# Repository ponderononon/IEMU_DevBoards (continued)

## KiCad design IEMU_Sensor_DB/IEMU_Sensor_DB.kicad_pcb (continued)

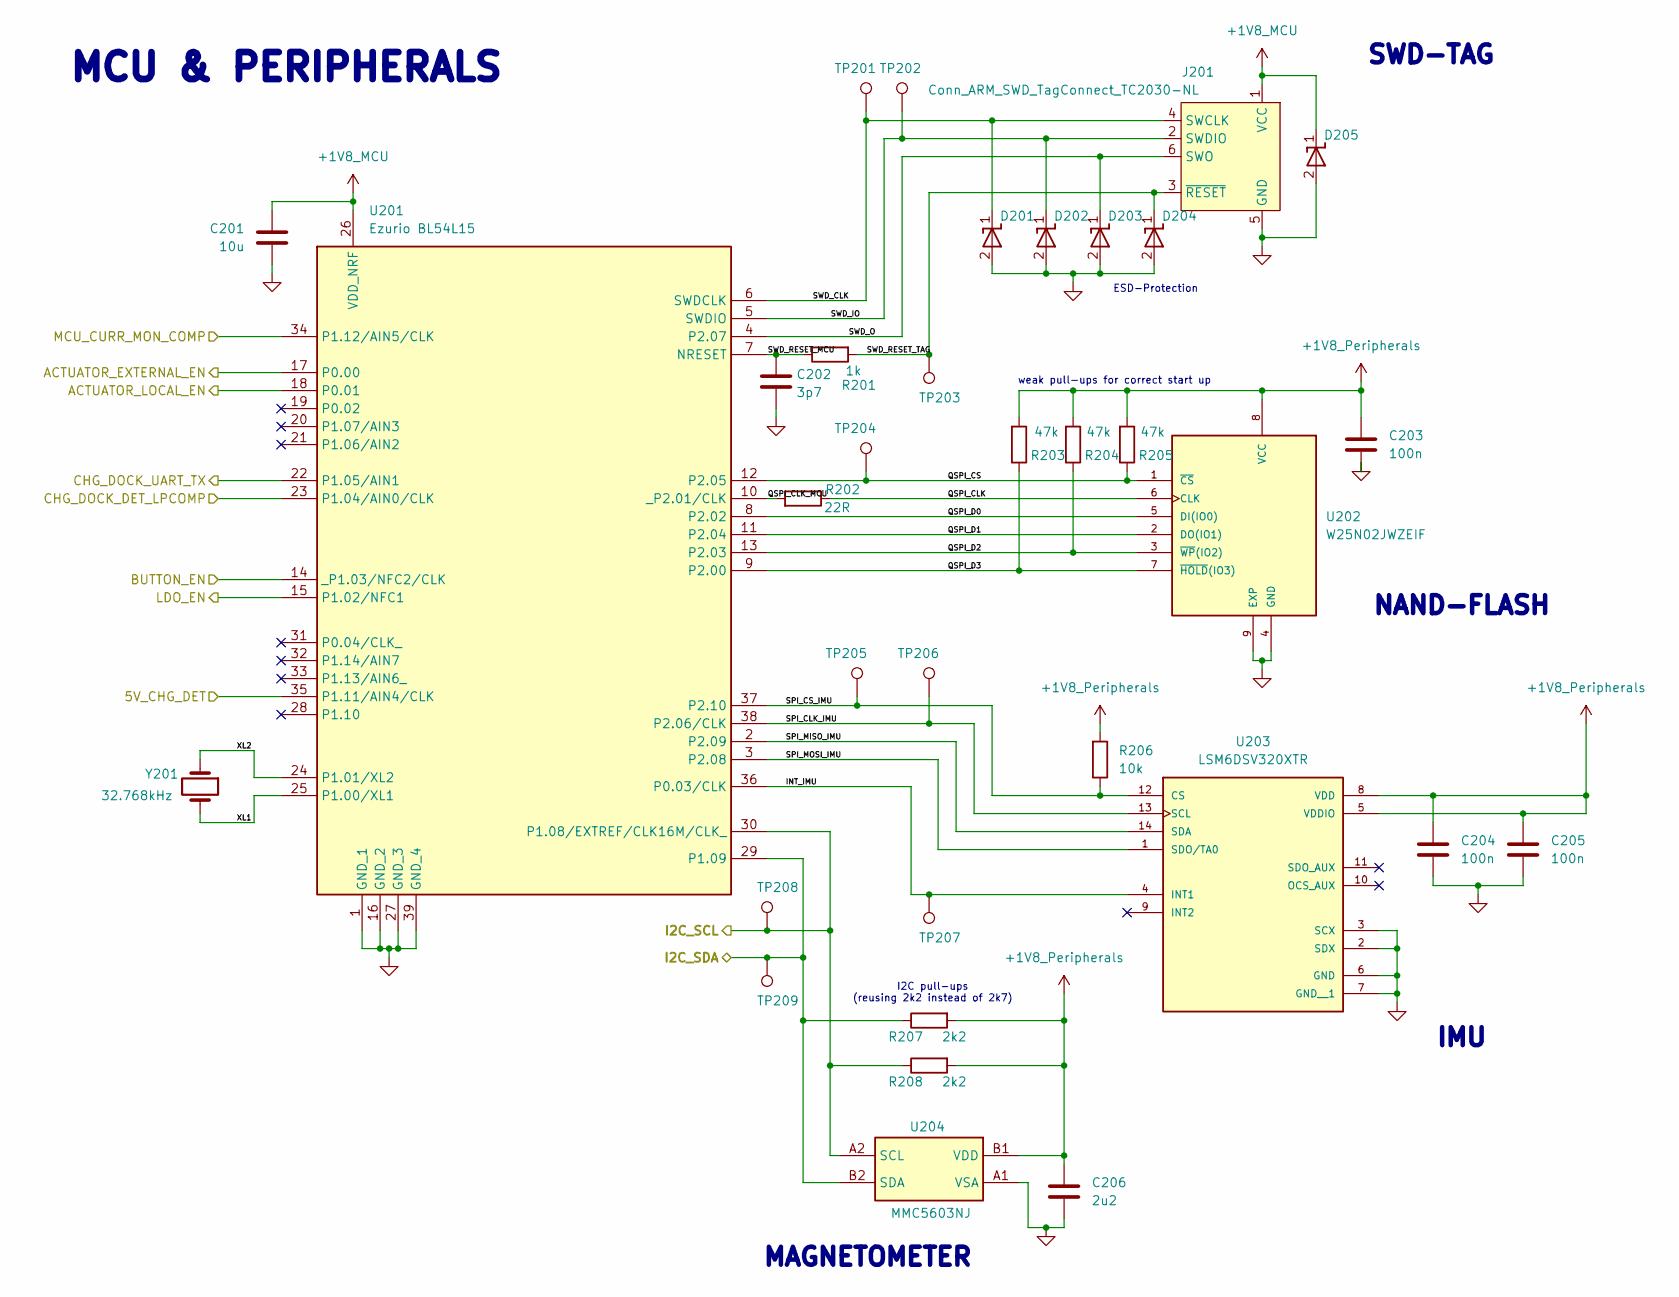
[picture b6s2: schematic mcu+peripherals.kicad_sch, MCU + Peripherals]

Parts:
C201: 10u; C_0603_1608Metric; Manufacturer_Part_Number CL10A106MA8NRNC; LCSC C96446
C202: 3p7; C_0402_1005Metric; Manufacturer_Part_Number GCM1555C1H3R7CA16D; LCSC C2189484
C203, C204, C205: 100n; C_0402_1005Metric; Manufacturer_Part_Number CL05B104KO5NNNC; LCSC C1525
C206: 2u2; C_0402_1005Metric; Manufacturer_Part_Number CL05A225MQ5NSNC; LCSC C12530
D201, D202, D203, D204, D205: RCLAMP01811PW.C; DIODFN100X60X55-2N; Manufacturer_Part_Number RCLAMP01811PW.C
J201: Conn_ARM_SWD_TagConnect_TC2030-NL; Tag-Connect_TC2030-IDC-NL_2x03_P1.27mm_Vertical
R201: 1k; R_0402_1005Metric; Manufacturer_Part_Number 0402WGF1001TCE; LCSC C11702
R202: 22R; R_0603_1608Metric; Manufacturer_Part_Number 0603WAF220JT5E; LCSC C23345
R203, R204, R205: 47k; R_0402_1005Metric; Manufacturer_Part_Number 0402WGF4702TCE; LCSC C25792
R206: 10k; R_0402_1005Metric; Manufacturer_Part_Number 0402WGF1002TCE; LCSC C25744
R207, R208: 2k2; R_0402_1005Metric; Manufacturer_Part_Number 0402WGF2201TCE; LCSC C25879
TP201, TP202, TP203, TP204, TP205, TP206, TP207, TP208, TP209: TestPoint_Pad_D1.0mm
U201: Ezurio BL54L15; BL54L15; Manufacturer_Part_Number 453-00001C
U202: W25N02JWZEIF; IC_W25N04KVZEIR; Manufacturer_Part_Number W25N02JWZEIF; LCSC C2962014
U203: LSM6DSV320XTR; LGA-14_3x2.5mm_P0.5mm_LayoutBorder3x4y; Manufacturer_Part_Number LSM6DSV320XTR; LCSC C26633007
U204: MMC5603NJ; Manufacturer_Part_Number MMC5603NJ; LCSC C404328
Y201: 32.768kHz; Crystal_SMD_3215-2Pin_3.2x1.5mm; Manufacturer_Part_Number SC-32S32.768kHz20PPM9pF; LCSC C97605

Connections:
+1V8_MCU: C201.1, D205.1 (I/O), J201.1 (VCC), U201.26 (VDD_NRF); also elsewhere on the board
+1V8_Peripherals: C203.1, C204.1, C205.1, C206.1, R203.1, R204.1, R205.1, R206.1, R207.1, R208.1, U202.8 (VCC), U203.5 (VDDIO), U203.8 (VDD), U204.B1 (VDD); also elsewhere on the board
/1_Power/5V_CHG_DET: U201.35 (P1.11/AIN4/CLK); also elsewhere on the board
/1_Power/CHG_DOCK_DET_LPCOMP: U201.23 (P1.04/AIN0/CLK); also elsewhere on the board
/1_Power/CHG_DOCK_UART_TX: U201.22 (P1.05/AIN1); also elsewhere on the board
/1_Power/LDO_EN: U201.15 (P1.02/NFC1); also elsewhere on the board
/1_Power/MCU_CURR_MON_COMP: U201.34 (P1.12/AIN5/CLK); also elsewhere on the board
/1_Power/NPM_SCL: R208.2, TP208.1, U201.30 (P1.08/EXTREF/CLK16M/CLK_), U204.A2 (SCL); also elsewhere on the board
/1_Power/NPM_SDA: R207.2, TP209.1, U201.29 (P1.09), U204.B2 (SDA); also elsewhere on the board
/2_nRF Module & NAND Flash + IMU + Magnetometer/ACTUATOR_EXTERNAL_EN: U201.17 (P0.00); also elsewhere on the board
/2_nRF Module & NAND Flash + IMU + Magnetometer/ACTUATOR_LOCAL_EN: U201.18 (P0.01); also elsewhere on the board
/2_nRF Module & NAND Flash + IMU + Magnetometer/BUTTON_EN: U201.14 (_P1.03/NFC2/CLK); also elsewhere on the board
/2_nRF Module & NAND Flash + IMU + Magnetometer/INT_IMU: TP207.1, U201.36 (P0.03/CLK), U203.4 (INT1)
/2_nRF Module & NAND Flash + IMU + Magnetometer/QSPI_CLK: R202.2, U202.6 (CLK)
/2_nRF Module & NAND Flash + IMU + Magnetometer/QSPI_CLK_MCU: R202.1, U201.10 (_P2.01/CLK)
/2_nRF Module & NAND Flash + IMU + Magnetometer/QSPI_CS: R205.2, TP204.1, U201.12 (P2.05), U202.1 (~CS)
/2_nRF Module & NAND Flash + IMU + Magnetometer/QSPI_D0: U201.8 (P2.02), U202.5 (DI(IO0))
/2_nRF Module & NAND Flash + IMU + Magnetometer/QSPI_D1: U201.11 (P2.04), U202.2 (DO(IO1))
/2_nRF Module & NAND Flash + IMU + Magnetometer/QSPI_D2: R204.2, U201.13 (P2.03), U202.3 (~WP(IO2))
/2_nRF Module & NAND Flash + IMU + Magnetometer/QSPI_D3: R203.2, U201.9 (P2.00), U202.7 (~HOLD(IO3))
/2_nRF Module & NAND Flash + IMU + Magnetometer/SPI_CLK_IMU: TP206.1, U201.38 (P2.06/CLK), U203.13 (SCL)
/2_nRF Module & NAND Flash + IMU + Magnetometer/SPI_CS_IMU: R206.2, TP205.1, U201.37 (P2.10), U203.12 (CS)
/2_nRF Module & NAND Flash + IMU + Magnetometer/SPI_MISO_IMU: U201.2 (P2.09), U203.14 (SDA)
/2_nRF Module & NAND Flash + IMU + Magnetometer/SPI_MOSI_IMU: U201.3 (P2.08), U203.1 (SDO/TA0)
/2_nRF Module & NAND Flash + IMU + Magnetometer/SWD_CLK: D201.1 (I/O), J201.4 (SWCLK), TP201.1, U201.6 (SWDCLK)
/2_nRF Module & NAND Flash + IMU + Magnetometer/SWD_IO: D202.1 (I/O), J201.2 (SWDIO), TP202.1, U201.5 (SWDIO)
/2_nRF Module & NAND Flash + IMU + Magnetometer/SWD_O: D203.1 (I/O), J201.6 (SWO), U201.4 (P2.07)
/2_nRF Module & NAND Flash + IMU + Magnetometer/SWD_RESET_MCU: C202.1, R201.2, U201.7 (NRESET)
/2_nRF Module & NAND Flash + IMU + Magnetometer/SWD_RESET_TAG: D204.1 (I/O), J201.3 (~RESET), R201.1, TP203.1
/2_nRF Module & NAND Flash + IMU + Magnetometer/XL1: U201.25 (P1.00/XL1), Y201.2
/2_nRF Module & NAND Flash + IMU + Magnetometer/XL2: U201.24 (P1.01/XL2), Y201.1
GND: C201.2, C202.2, C203.2, C204.2, C205.2, C206.2, D201.2 (GND), D202.2 (GND), D203.2 (GND), D204.2 (GND), D205.2 (GND), J201.5 (GND), U201.1 (GND_1), U201.16 (GND_2), U201.27 (GND_3), U201.39 (GND_4), U202.4 (GND), U202.9 (EXP), U203.2 (SDX), U203.3 (SCX), U203.6 (GND), U203.7 (GND__1), U204.A1 (VSA); also elsewhere on the board

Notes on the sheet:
I2C pull-ups (reusing 2k2 instead of 2k7)
MAGNETOMETER
IMU
SWD-TAG
MCU & PERIPHERALS
NAND-FLASH
weak pull-ups for correct start up
ESD-Protection

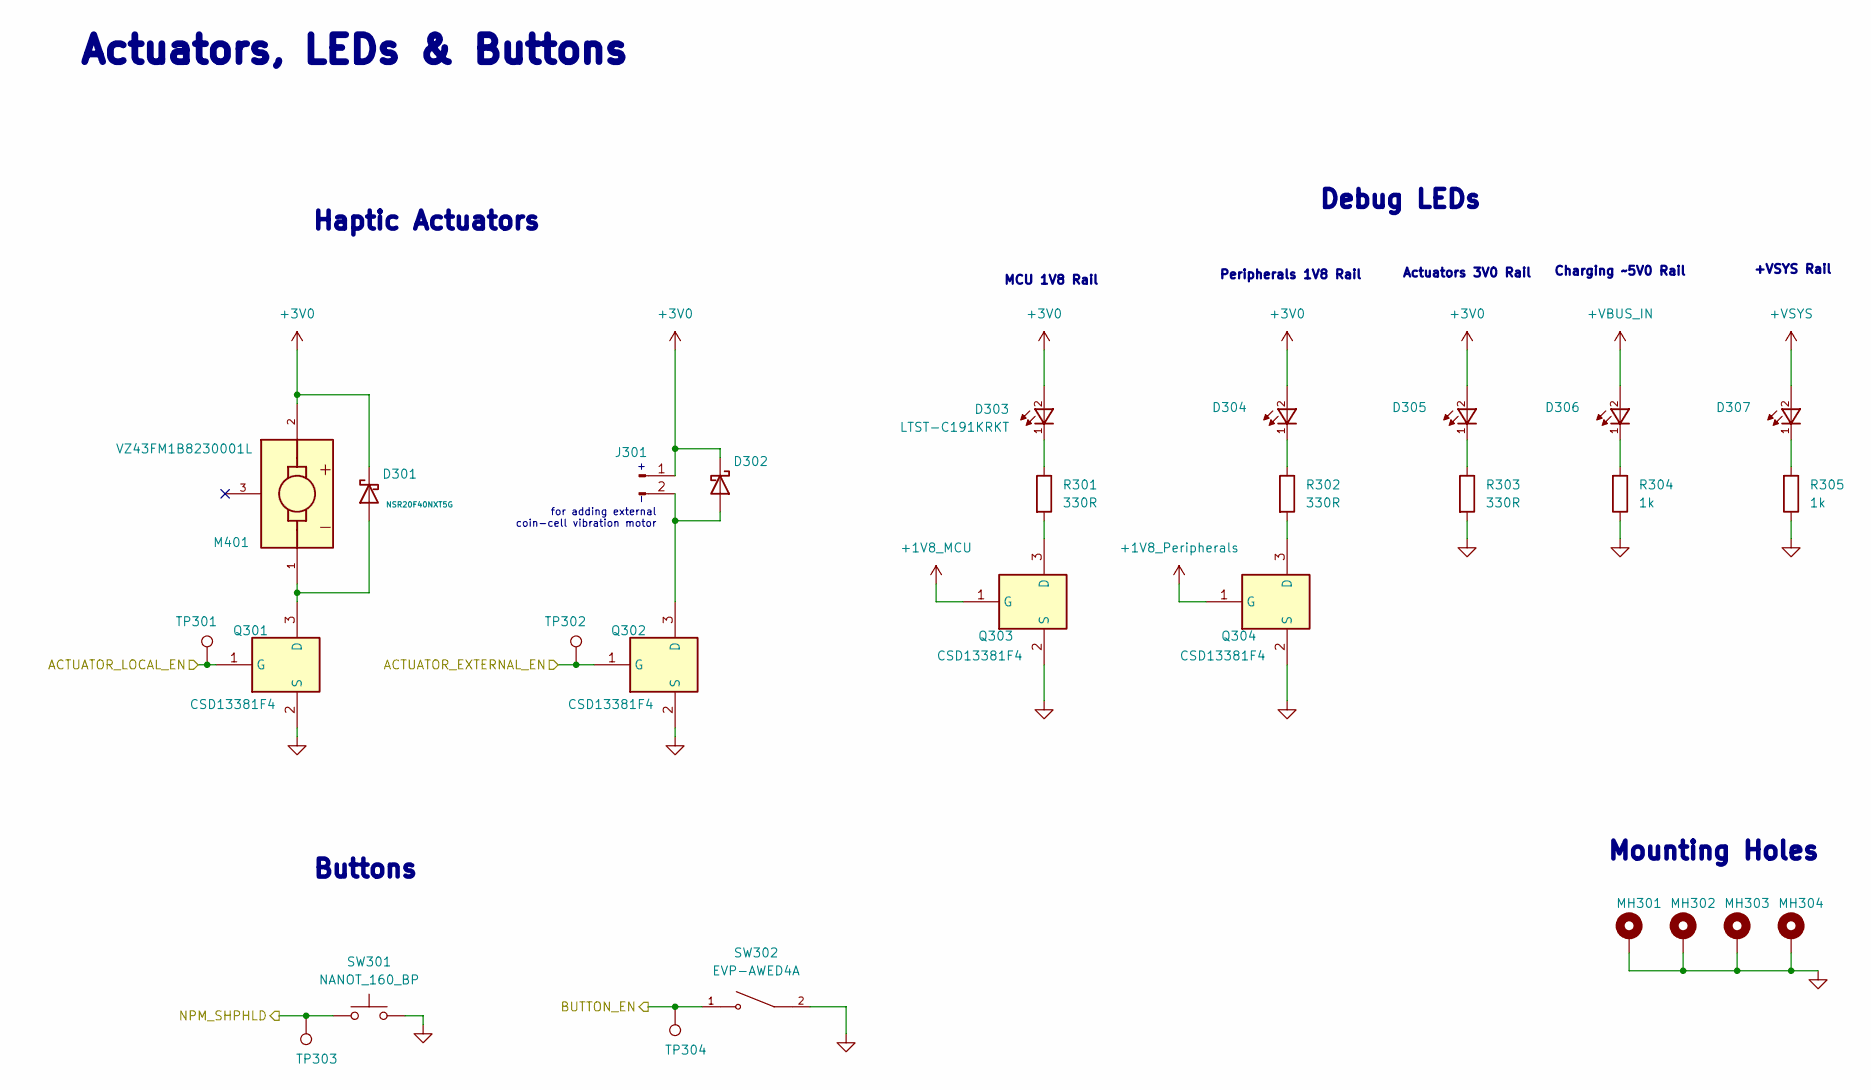
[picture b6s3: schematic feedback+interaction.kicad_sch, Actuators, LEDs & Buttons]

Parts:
D301, D302: D_Schottky_2A_40V_0603; 0603_DSN; Manufacturer_Part_Number NSR20F40NXT5G; LCSC C153761
D303, D304, D305, D306, D307: LTST-C191KRKT; Manufacturer_Part_Number LTST-C191KRKT; LCSC C125099
J301: Conn_01x02_Pin; SolderWire-0.5sqmm_1x02_P4.6mm_D0.9mm_OD2.1mm
M401: VZ43FM1B8230001L; XDCR_VZ43FM1B8230001L; Manufacturer_Part_Number VZ43FM1B8230001L; LCSC C7467059
MH301, MH302, MH303, MH304: MountingHole_Pad; MountingHole_2.2mm_M2_Pad_Via
Q301, Q302, Q303, Q304: CSD13381F4; DFN100X60X35-3N; Manufacturer_Part_Number CSD13381F4; LCSC C179868
R301, R302, R303: 330R; R_0402_1005Metric; Manufacturer_Part_Number 0402WGF3300TCE; LCSC C25104
R304, R305: 1k; R_0402_1005Metric; Manufacturer_Part_Number 0402WGF1001TCE; LCSC C11702
SW301: NANOT_160_BP; NANOT160BP; Manufacturer_Part_Number NANOT160BP; LCSC C2760983
SW302: EVP-AWED4A; SW_EVP-AWED4A; Manufacturer_Part_Number EVP-AWBD2A
TP301, TP302, TP303, TP304: TestPoint_Pad_D1.0mm

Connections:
+1V8_MCU: Q303.1 (G); also elsewhere on the board
+1V8_Peripherals: Q304.1 (G); also elsewhere on the board
+3V0: D301.1 (K), D302.1 (K), D303.2, D304.2, D305.2, J301.1, M401.2; also elsewhere on the board
+VBUS_IN: D306.2; also elsewhere on the board
+VSYS: D307.2; also elsewhere on the board
/1_Power/NPM_SHPHLD: SW301.1, TP303.1; also elsewhere on the board
/2_nRF Module & NAND Flash + IMU + Magnetometer/ACTUATOR_EXTERNAL_EN: Q302.1 (G), TP302.1; also elsewhere on the board
/2_nRF Module & NAND Flash + IMU + Magnetometer/ACTUATOR_LOCAL_EN: Q301.1 (G), TP301.1; also elsewhere on the board
/2_nRF Module & NAND Flash + IMU + Magnetometer/BUTTON_EN: SW302.1, TP304.1; also elsewhere on the board
GND: MH301.1, MH302.1, MH303.1, MH304.1, Q301.2 (S), Q302.2 (S), Q303.2 (S), Q304.2 (S), R303.2, R304.2, R305.2, SW301.2, SW302.2; also elsewhere on the board
unnamed: D301.2 (A), M401.1, Q301.3 (D)
unnamed: D302.2 (A), J301.2, Q302.3 (D)
unnamed: D303.1, R301.1
unnamed: D304.1, R302.1
unnamed: D305.1, R303.1
unnamed: D306.1, R304.1
unnamed: D307.1, R305.1
unnamed: Q303.3 (D), R301.2
unnamed: Q304.3 (D), R302.2

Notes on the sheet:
Actuators 3V0 Rail
Mounting Holes
Buttons
Actuators, LEDs & Buttons
Peripherals 1V8 Rail
for adding external coin-cell vibration motor
+VSYS Rail
MCU 1V8 Rail
Haptic Actuators
Charging ~5V0 Rail
Debug LEDs

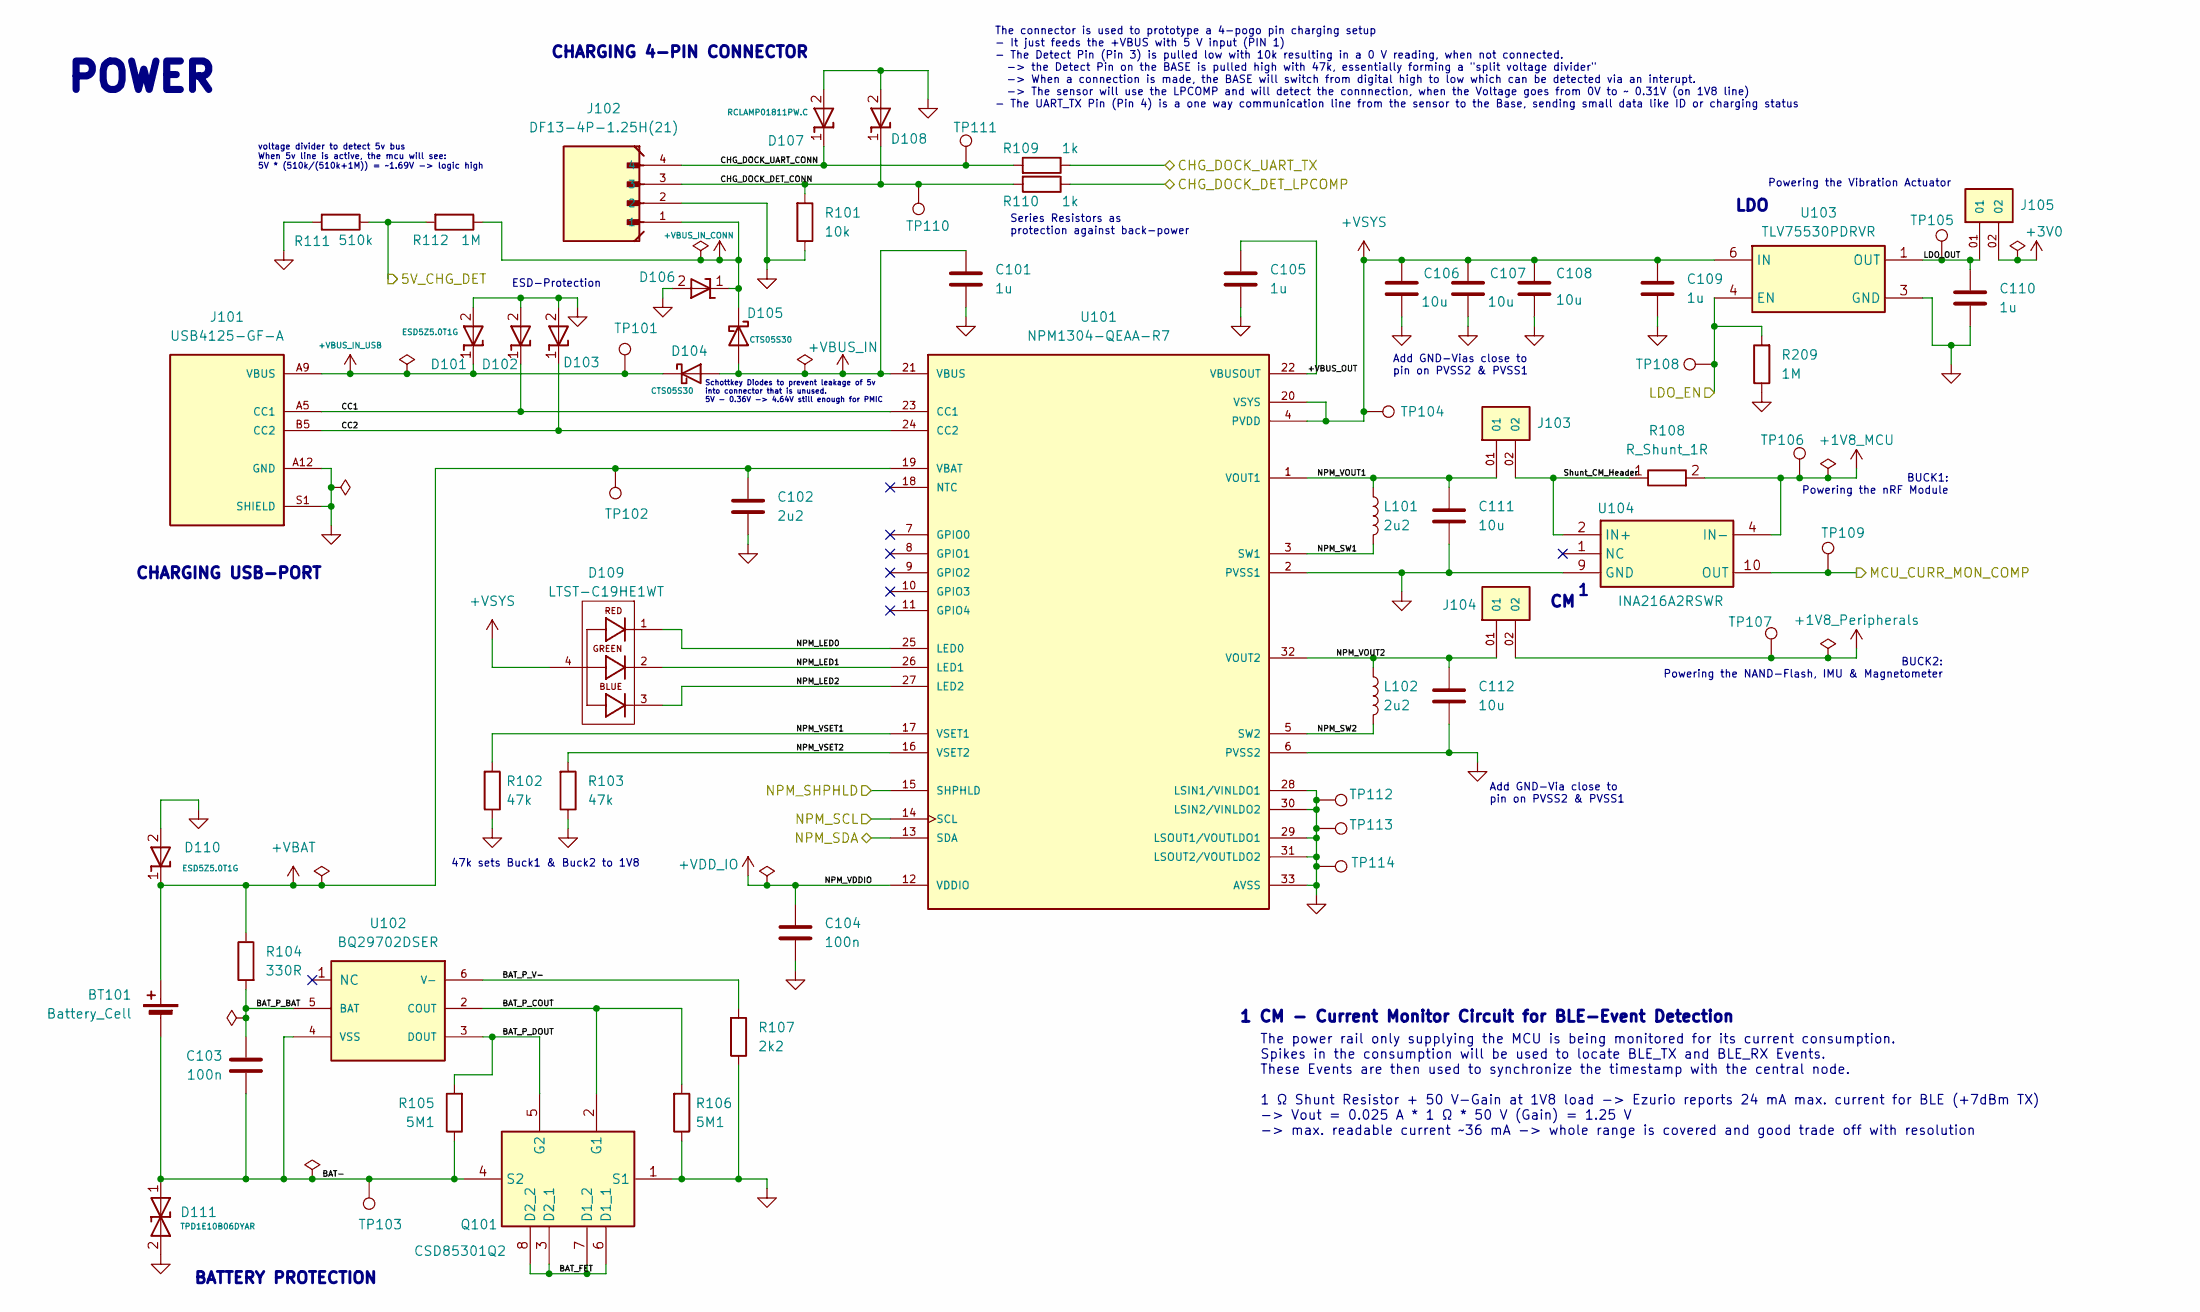
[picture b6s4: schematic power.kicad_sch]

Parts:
BT101: Battery_Cell; CoinCell_LIR1455_LBY2
C101, C105, C109, C110: 1u; C_0402_1005Metric; Manufacturer_Part_Number CL05A105KA5NQNC; LCSC C52923
C102: 2u2; C_0402_1005Metric; Manufacturer_Part_Number CL05A225MQ5NSNC; LCSC C12530
C103, C104: 100n; C_0402_1005Metric; Manufacturer_Part_Number CL05B104KO5NNNC; LCSC C1525
C106, C107, C108, C111, C112: 10u; C_0603_1608Metric; Manufacturer_Part_Number CL10A106MA8NRNC; LCSC C96446
D101, D102, D103, D106, D110: ESD5Z5.0T1G; D_SOD-523_1; Manufacturer_Part_Number ESD5Z5.0T1G; LCSC C82044
D104, D105: CTS05S30; D_SOD-882; Manufacturer_Part_Number CTS05S30
D107, D108: RCLAMP01811PW.C; DIODFN100X60X55-2N; Manufacturer_Part_Number RCLAMP01811PW.C
D109: LTST-C19HE1WT; LED_LTST-C19HE1WT; Manufacturer_Part_Number LTST-C19HE1WT; LCSC C458749
D111: TPD1E10B06DYAR; D_SOD-523; Manufacturer_Part_Number TPD1E10B06DYAR; LCSC C3712135
J101: USB4125-GF-A; GCT_USB4125-GF-A_REVA2; Manufacturer_Part_Number USB4125-GF-A; LCSC C3151650
J102: DF13-4P-1.25H(21); Manufacturer_Part_Number DF13-4P-1.25H(21); LCSC C597872
J103, J104, J105: SAMTEC_MTSW-101-X-X-D-X; Manufacturer_Part_Number MTSW-101-07-T-D-240
L101, L102: 2u2; L_0603_1608Metric; Manufacturer_Part_Number LSCNB1608HKT2R2MD; LCSC C6079477
Q101: CSD85301Q2; Manufacturer_Part_Number CSD85301Q2; LCSC C544396
R101: 10k; R_0402_1005Metric; Manufacturer_Part_Number 0402WGF1002TCE; LCSC C25744
R102, R103: 47k; R_0402_1005Metric; Manufacturer_Part_Number 0402WGF4702TCE; LCSC C25792
R104: 330R; R_0402_1005Metric; Manufacturer_Part_Number 0402WGF3300TCE; LCSC C25104
R105, R106: 5M1; R_0402_1005Metric; Manufacturer_Part_Number RC0402JR-075M1L; LCSC C137855
R107: 2k2; R_0402_1005Metric; Manufacturer_Part_Number 0402WGF2201TCE; LCSC C25879
R108: R_Shunt_1R; R_0402_1005Metric; Manufacturer_Part_Number RLP73K1E1R0FTDF; LCSC C2074826
R109, R110: 1k; R_0402_1005Metric; Manufacturer_Part_Number 0402WGF1001TCE; LCSC C11702
R111: 510k; R_0603_1608Metric; Manufacturer_Part_Number 0603WAF5103T5E; LCSC C23192
R112, R209: 1M; R_0402_1005Metric; Manufacturer_Part_Number 0402WGF1004TCE; LCSC C26083
TP101, TP102, TP103, TP104, TP105, TP106, TP107, TP108, TP109, TP110, TP111, TP112, TP113, TP114: TestPoint_Pad_D1.0mm
U101: NPM1304-QEAA-R7; QFN50P500X500X90-33N; Manufacturer_Part_Number NPM1304-QEAA-R7; LCSC C49448846
U102: BQ29702DSER; WSON-6_1.5x1.5mm_P0.5mm; Manufacturer_Part_Number BQ29702DSER; LCSC C2872632
U103: TLV75530PDRVR; WSON-6-1EP_2x2mm_P0.65mm_EP1x1.6mm_ThermalVias; Manufacturer_Part_Number TLV75530PDRVR; LCSC C2859948
U104: INA216A2RSWR; Texas_RSW0010A_UQFN-10_1.4x1.8mm_P0.4mm; Manufacturer_Part_Number INA216A2RSWR; LCSC C2653823

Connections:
+1V8_MCU: R108.2, TP106.1, U104.4 (IN-), U104.5 (IN-); also elsewhere on the board
+1V8_Peripherals: J104.02, TP107.1; also elsewhere on the board
+3V0: J105.02; also elsewhere on the board
+VBAT: BT101.1 (+), C102.1, D110.1 (I/O), R104.1, TP102.1, U101.19 (VBAT)
+VBUS_IN: C101.1, D104.2 (A), D105.2 (A), U101.21 (VBUS); also elsewhere on the board
+VBUS_IN_CONN: D105.1 (K), D106.1 (I/O), J102.1, R112.2
+VBUS_IN_USB: D101.1 (I/O), D104.1 (K), J101.A9 (VBUS), J101.B9 (VBUS), TP101.1
+VDD_IO: C104.1, U101.12 (VDDIO)
+VSYS: C106.1, C107.1, C108.1, C109.1, D109.4, TP104.1, U101.4 (PVDD), U101.20 (VSYS), U103.6 (IN); also elsewhere on the board
/1_Power/5V_CHG_DET: R111.2, R112.1; also elsewhere on the board
/1_Power/+VBUS_OUT: C105.1, U101.22 (VBUSOUT)
/1_Power/BAT-: BT101.2 (-), C103.2, D111.1 (I/O), Q101.4 (S2), R105.2, TP103.1, U102.4 (VSS)
/1_Power/BAT_FET: Q101.3 (D2_1), Q101.6 (D1_1), Q101.7 (D1_2), Q101.8 (D2_2)
/1_Power/BAT_P_BAT: C103.1, R104.2, U102.5 (BAT)
/1_Power/BAT_P_COUT: Q101.2 (G1), R106.1, U102.2 (COUT)
/1_Power/BAT_P_DOUT: Q101.5 (G2), R105.1, U102.3 (DOUT)
/1_Power/BAT_P_V-: R107.1, U102.6 (V-)
/1_Power/CC1: D102.1 (I/O), J101.A5 (CC1), U101.23 (CC1)
/1_Power/CC2: D103.1 (I/O), J101.B5 (CC2), U101.24 (CC2)
/1_Power/CHG_DOCK_DET_CONN: D108.1 (I/O), J102.3, R101.1, R110.1, TP110.1
/1_Power/CHG_DOCK_DET_LPCOMP: R110.2; also elsewhere on the board
/1_Power/CHG_DOCK_UART_CONN: D107.1 (I/O), J102.4, R109.1, TP111.1
/1_Power/CHG_DOCK_UART_TX: R109.2; also elsewhere on the board
/1_Power/LDO_EN: R209.1, TP108.1, U103.4 (EN); also elsewhere on the board
/1_Power/LDO_OUT: C110.1, J105.01, TP105.1, U103.1 (OUT)
/1_Power/MCU_CURR_MON_COMP: TP109.1, U104.10 (OUT); also elsewhere on the board
/1_Power/NPM_LED0: D109.1, U101.25 (LED0)
/1_Power/NPM_LED1: D109.2, U101.26 (LED1)
/1_Power/NPM_LED2: D109.3, U101.27 (LED2)
/1_Power/NPM_SCL: U101.14 (SCL); also elsewhere on the board
/1_Power/NPM_SDA: U101.13 (SDA); also elsewhere on the board
/1_Power/NPM_SHPHLD: U101.15 (SHPHLD); also elsewhere on the board
/1_Power/NPM_SW1: L101.2, U101.3 (SW1)
/1_Power/NPM_SW2: L102.2, U101.5 (SW2)
/1_Power/NPM_VOUT1: C111.1, J103.01, L101.1, U101.1 (VOUT1)
/1_Power/NPM_VOUT2: C112.1, J104.01, L102.1, U101.32 (VOUT2)
/1_Power/NPM_VSET1: R102.1, U101.17 (VSET1)
/1_Power/NPM_VSET2: R103.1, U101.16 (VSET2)
/1_Power/Shunt_CM_Header: J103.02, R108.1, U104.2 (IN+), U104.3 (IN+)
GND: C101.2, C102.2, C104.2, C105.2, C106.2, C107.2, C108.2, C109.2, C110.2, C111.2, C112.2, D101.2 (GND), D102.2 (GND), D103.2 (GND), D106.2 (GND), D107.2 (GND), D108.2 (GND), D110.2 (GND), D111.2 (GND), J101.A12 (GND), J101.B12 (GND), J101.S1 (SHIELD), J101.S2 (SHIELD), J101.S3 (SHIELD), J101.S4 (SHIELD), J102.2, Q101.1 (S1), R101.2, R102.2, R103.2, R106.2, R107.2, R111.1, R209.2, TP112.1, TP113.1, TP114.1, U101.2 (PVSS1), U101.6 (PVSS2), U101.28 (LSIN1/VINLDO1), U101.29 (LSOUT1/VOUTLDO1), U101.30 (LSIN2/VINLDO2), U101.31 (LSOUT2/VOUTLDO2), U101.33 (AVSS), U103.2 (NC), U103.3 (GND), U103.5 (NC), U103.7 (GND), U104.9 (GND); also elsewhere on the board

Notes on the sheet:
POWER
BUCK2: Powering the NAND-Flash, IMU & Magnetometer
Powering the Vibration Actuator
LDO
Schottkey Diodes to prevent leakage of 5v into connector that is unused. 5V - 0.36V -> 4.64V still enough for PMIC
BUCK1: Powering the nRF Module
47k sets Buck1 & Buck2 to 1V8
CHARGING USB-PORT
ESD-Protection
Add GND-Vias close to pin on PVSS2 & PVSS1
Series Resistors as protection against back-power
Add GND-Via close to pin on PVSS2 & PVSS1
1 CM - Current Monitor Circuit for BLE-Event Detection
voltage divider to detect 5v bus When 5v line is active, the mcu will see: 5V * (510k/(510k+1M)) = ~1.69V -> logic high
The connector is used to prototype a 4-pogo pin charging setup - It just feeds the +VBUS with 5 V input (PIN 1) - The Detect Pin (Pin 3) is pulled low with 10k resulting in a 0 V reading, when not connected. -> the Detect Pin on the BASE is pulled high with 47k, essentially forming a "split voltage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
BATTERY PROTECTION
CHARGING 4-PIN CONNECTOR
The power rail only supplying the MCU is being monitored for its current consumption. Spikes in the consumption will be used to locate BLE_TX and BLE_RX Events. These Events are then used to synchronize the timestamp with the central node. 1 Ω Shunt Resistor + 50 V-Gain at 1V8 load -> Ezurio report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

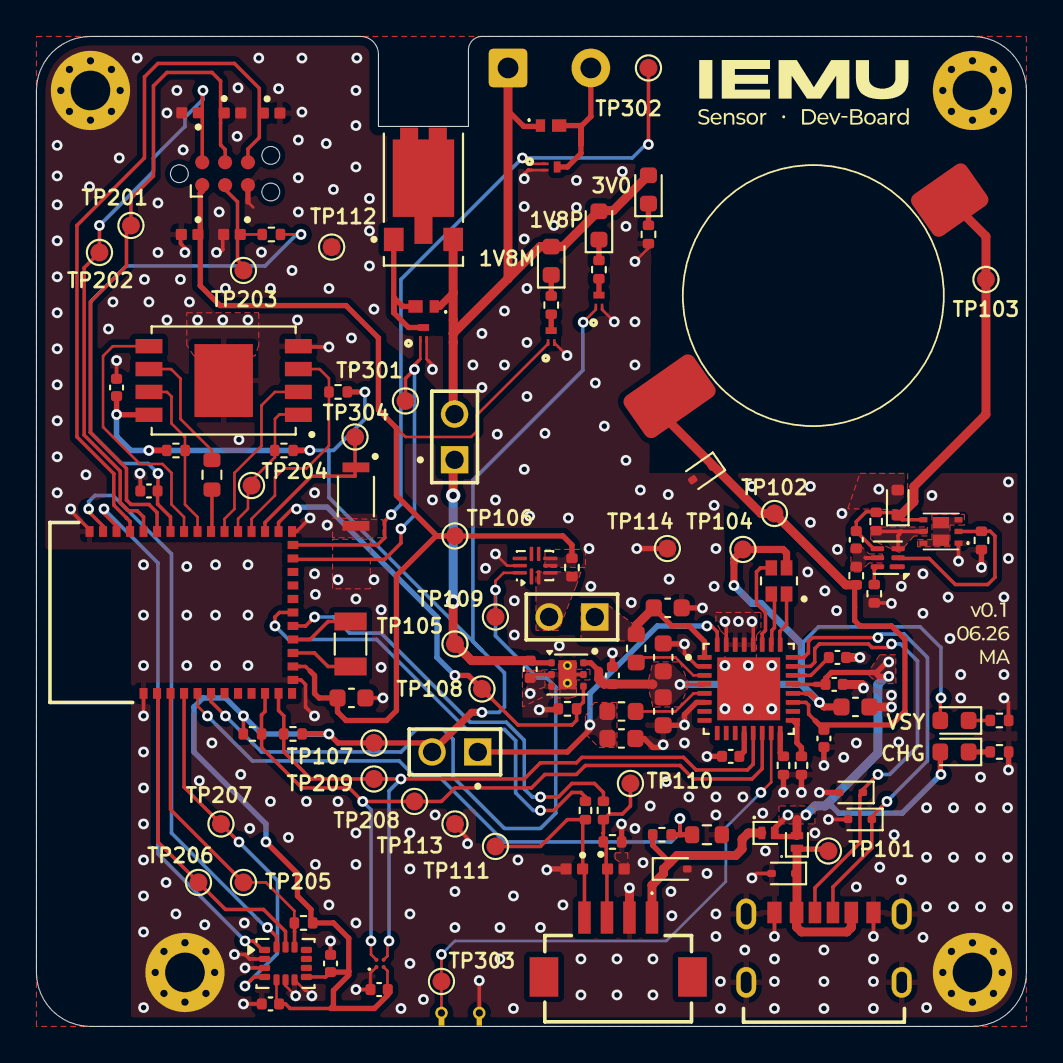
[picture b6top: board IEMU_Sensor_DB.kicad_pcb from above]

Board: 4 copper layers, 55.0 x 55.0 mm, 125 parts (0 on the bottom side), 71 nets.

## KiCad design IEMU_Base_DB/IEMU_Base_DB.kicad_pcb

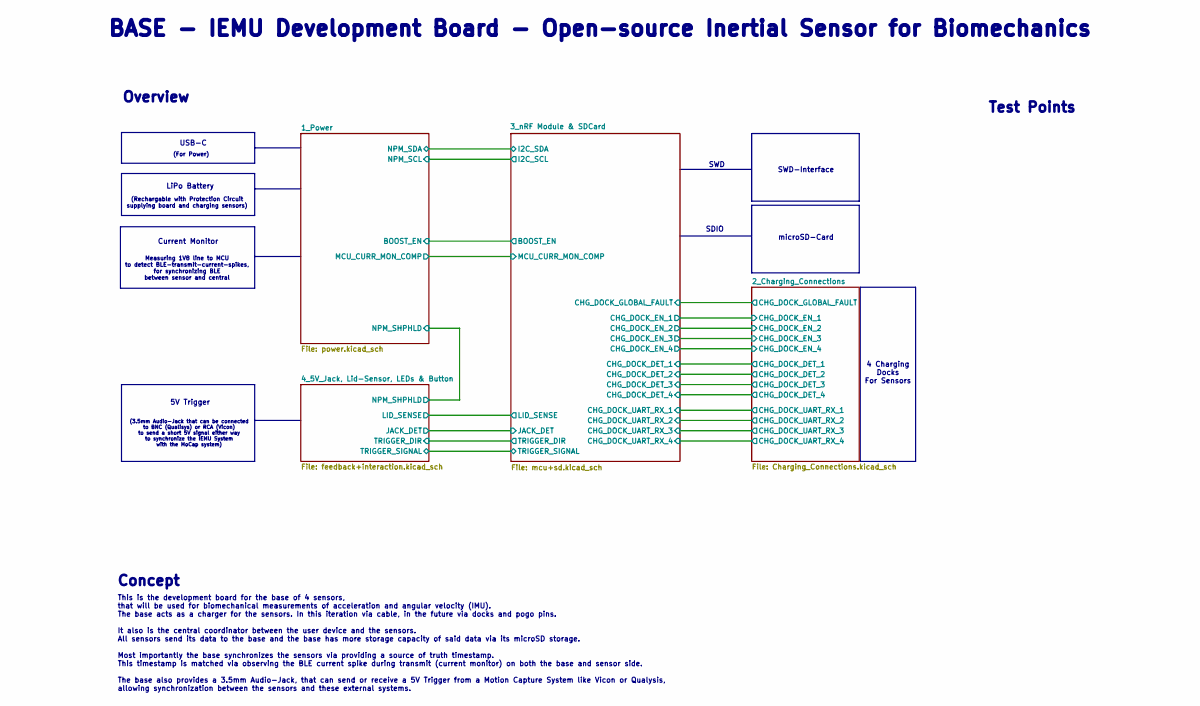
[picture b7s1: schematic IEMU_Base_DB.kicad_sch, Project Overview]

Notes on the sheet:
(Rechargable with Protection Circuit supplying board and charging sensors)
SWD
Current Monitor
(3.5mm Audio-Jack that can be connected to BNC (Qualisys) or RCA (Vicon) to send a short 5V signal either way to synchronize the IEMU System with the MoCap system)
Concept
USB-C
This is the development board for the base of 4 sensors, that will be used for biomechanical measurements of acceleration and angular velocity (IMU). The base acts as a charger for the sensors. In this iteration via cable, in the future via docks and pogo pins. It also is the central coordinator be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
microSD-Card
(For Power)
LiPo Battery
SWD-Interface
Measuring 1V8 line to MCU to detect BLE-transmit-current-spikes, for synchronizing BLE between sensor and central
Test Points
4 Charging Docks For Sensors
SDIO
Overview
5V Trigger
BASE - IEMU Development Board - Open-source Inertial Sensor for Biomechanics
